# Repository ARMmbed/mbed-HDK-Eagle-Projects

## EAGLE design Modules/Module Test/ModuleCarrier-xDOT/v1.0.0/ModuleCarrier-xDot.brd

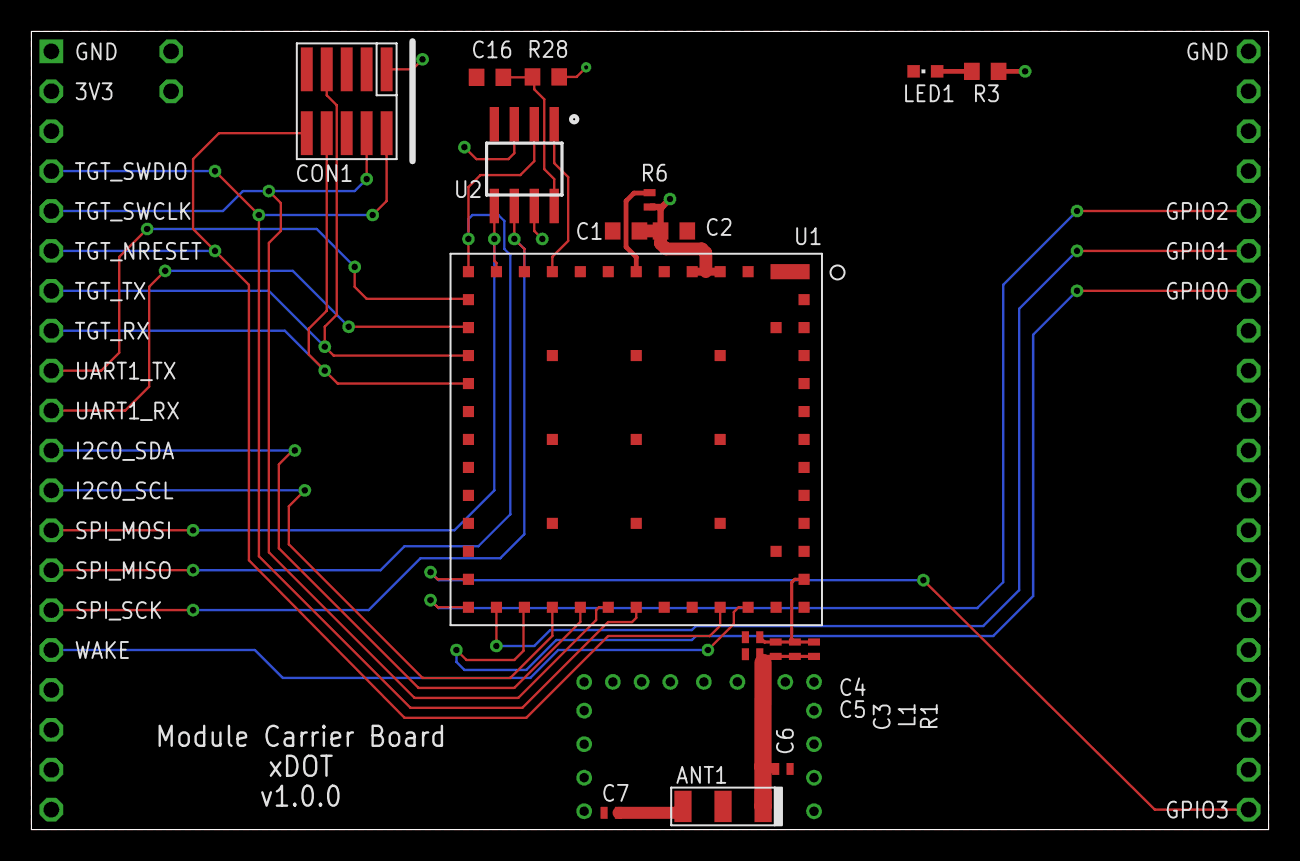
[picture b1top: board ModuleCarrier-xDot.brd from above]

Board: 2 copper layers, 78.7 x 50.8 mm, 21 parts (0 on the bottom side), 26 nets.

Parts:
ANT1: M620720
C1: 10uF; 0603
C2, C16: 100nF; 0603
C3: 9.1pF; 0402
C4: 5.6pF; 0402
C5: 10pF; 0402
C6: 82pF; 0402
C7: 6.8pF; 0402
CON1: SWD-10/TC2050_SMD; FTSH-105-02
L1: 7.5nH; 0402
LED1: SMD_LED0603; CHIPLED_0603
R1, R6: 0; 0402
R3: 1.5K; 0603
R28: 0; 0603
TP1, TP2: TEST-POINT-50R-PTH; TP50-PTH
U1: MTXDOT-EU1-A00-1; MTXDOT-EU1/NA1-A00-1
U2: MX25R3235FM1IH0; SO8
U$1: MODULE_DAUGHTER

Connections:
+3.3V_TGT: C1.1, C2.1, CON1.1, R3.2, R6.1, R28.2, TP1.TP, U1.P$3, U1.P$4, U2.3, U2.7, U$1.2
ANT1: C3.1, C4.2, L1.1, R1.1, U1.P$37
GND: C1.2, C2.2, C4.1, C5.1, C6.1, C7.1, C16.1, CON1.3, CON1.5, CON1.9, LED1.C, TP2.TP, U1.P$1, U1.P$5, U1.P$17, U1.P$20, U1.P$35, U1.P$36, U1.P$38, U1.P$39, U1.P$40, U1.P$41, U1.P$42, U1.P$43, U1.P$44, U1.P$45, U1.P$46, U1.P$48, U1.P$49, U1.P$50, U1.P$51, U1.P$52, U1.P$53, U1.P$54, U1.P$55, U1.P$56, U1.P$57, U1.P$58, U2.4, U$1.1
GPIO0: U1.P$26, U$1.34
GPIO1: U1.P$25, U$1.35
GPIO2: U1.P$24, U$1.36
GPIO3: U1.P$23, U$1.21
I2C0_SCL: U1.P$27, U$1.12
I2C0_SDA: U1.P$28, U$1.11
unnamed: ANT1.P$3, C7.2
unnamed: LED1.A, R3.1
unnamed: ANT1.P$1, C3.2, C5.2, C6.2, L1.2, R1.2
unnamed: C16.2, R28.1, U2.8
RFU2: R6.2, U1.P$6
SPI_MISO: U1.P$12, U2.2, U$1.14
SPI_MOSI: U1.P$11, U2.5, U$1.13
SPI_NSS: U1.P$9, U2.1
SPI_SCK: U1.P$10, U2.6, U$1.15
TGT_NRESET: CON1.10, U1.P$33, U$1.6
TGT_RX: CON1.8, U1.P$16, U$1.8
TGT_SWCLK: CON1.4, U1.P$29, U$1.5
TGT_SWDIO: CON1.2, U1.P$30, U$1.4
TGT_TX: CON1.7, U1.P$15, U$1.7
UART1_RX: U1.P$14, U$1.10
UART1_TX: U1.P$13, U$1.9
WAKE: U1.P$34, U$1.16

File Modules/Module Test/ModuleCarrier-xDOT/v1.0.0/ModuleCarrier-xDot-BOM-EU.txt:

Partlist exported from C:/Users/cstyles/Documents/mbed/Projects/blackbriar/ModuleCarrier-xDot/ModuleCarrier-xDot.sch at 16/11/2017 15:48

Do Not Populate:

	R1
	L1
	C5



Qty Value             Device            Package              Parts   Description                                                                                          MF                      MFN              OC-DIGIKEY    OC-MOUSER         OC-NEWARK
2   0                 RESISTOR0402      0402                 	R1, R6  Resistor                                                                                                                                                                               
1   0                 RESISTOR0603      0603                 	R28     Resistor                                                                                                                                                                               
1   1.5K              RESISTOR0402      0402                 	R3      Resistor                                                                                                                                                                               
2   100nF             CAPACITOR0603     0603                 	C2, C16 Capacitor                                                                                                                                                                              
1   10pF              CAPACITOR0402     0402                 	C5      Capacitor                                                                                                                                                                              
1   10uF              CAPACITOR0603     0603                 	C1      Capacitor                                                                                                                                                                              
1   5.6pF             CAPACITOR0402     0402                 	C4      Capacitor                                                                                                                                                                              
1   6.8pF             CAPACITOR0402     0402                 	C7      Capacitor  (4.7pF for 900MHz/US, 6.8pF for 800MHz/EU)                                                                                                                                                                              
1   7.5nH             INDUCTOR0402      0402                 	L1      Inductor                                                                                                                                                                               
1   82pF              CAPACITOR0402     0402                 	C6      Capacitor                                                                                                                                                                              
1   9.1pF             CAPACITOR0402     0402                 	C3      Capacitor                                                                                                                                                                              
1   M620720           M620720           M620720              	ANT1    Chip Antenna Ceramic ISM/M2M/IoT 868/915MHz                                                          Ethertronics            M620720          939-1066-1-ND                                                                                                                                                                       
1   MTXDOT-EU1-A00-1  MTXDOT-EU1-A00-1  MTXDOT-EU1-A00-1 	U1      Multitech xDOT LORA MODULE UFL/TRC 868MHz for Europe                                                 Multi-Tech Systems Inc. MTXDOT-EU1-A00-1 591-1292-ND                              
1   MX25R3235FM1IH0   MX25R3235FM1IH0   SO8                  	U2      Serial Flash 32 Mb 80 Mhz                                                                            Macronix                MX25R3235FM2IH0  1092-1174-ND                             
1   SMD_LED0603       SMD_LED0603       CHIPLED_0603         	LED2    LED SMD, Colour Red                                                                                  Wurth Electronics Inc   150060RS75000    732-4978-1-ND 710-150060RS75000 2322071  
1   SWD-10/TC2050_SMD SWD-10/TC2050_SMD FTSH-105-02          	CON1    1mm pitch 10-Pin Cortex Programming Header with optional TC2050 footprint solderless interchangeable

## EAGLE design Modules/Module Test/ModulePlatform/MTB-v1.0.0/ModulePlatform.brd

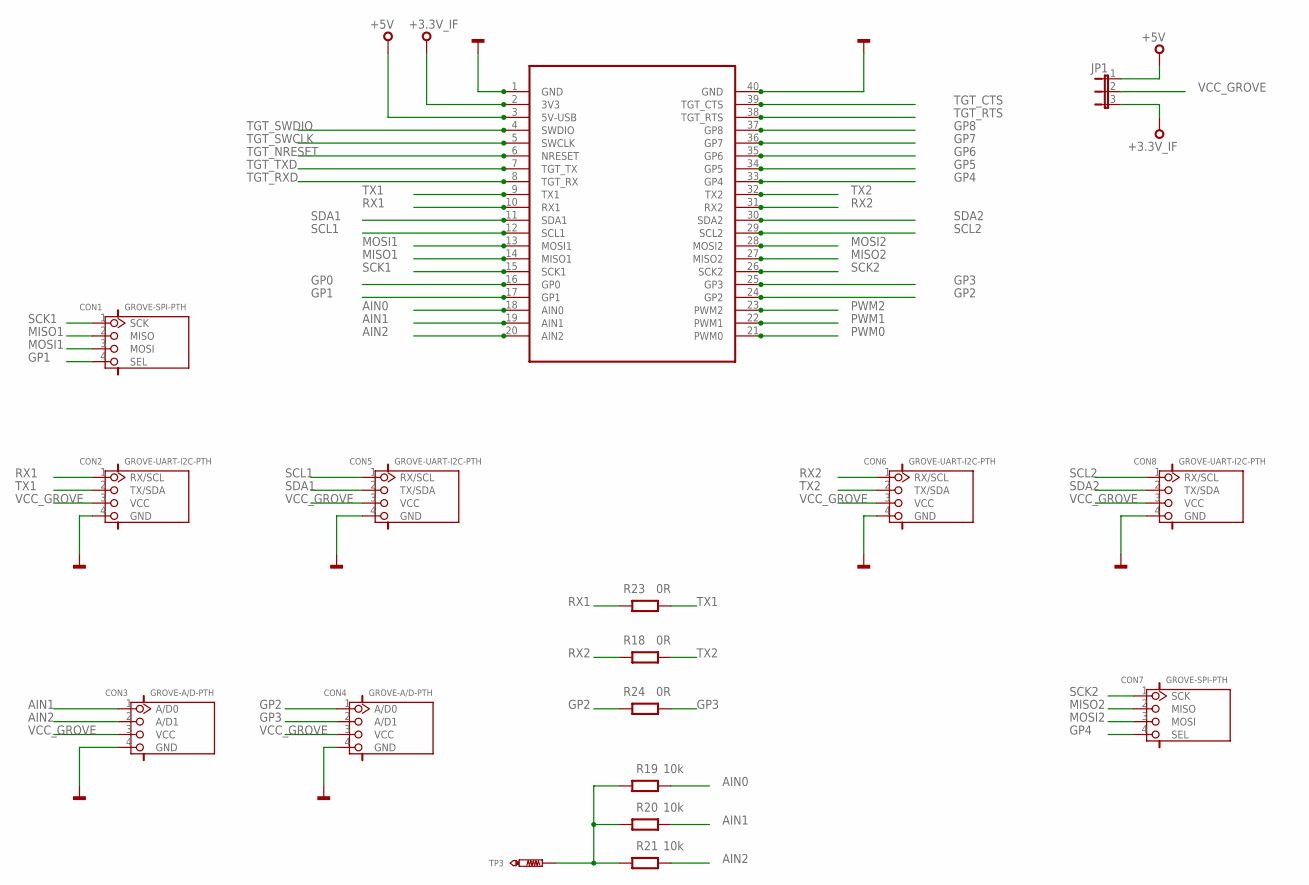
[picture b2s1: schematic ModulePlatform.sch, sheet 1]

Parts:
CON1, CON7: GROVE-SPI-PTH; HW4-2.0
CON2, CON5, CON6, CON8: GROVE-UART-I2C-PTH; HW4-2.0
CON3, CON4: GROVE-A/D-PTH; HW4-2.0
JP1: JP2E; JP2
R18, R23, R24: 0R; 0603@1
R19, R20, R21: 10k; 0603@1
SKT1: MODULE_SOCKET
TP3: TEST-POINT-50R-PTH; TP50-PTH

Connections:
+3.3V_IF: JP1.3, SKT1.2 (3V3), SKT1.P$42; also elsewhere on the board
+5V: JP1.1, SKT1.3 (5V-USB), SKT1.P$43; also elsewhere on the board
AIN0: R19.1, SKT1.18 (AIN0), SKT1.P$58; also elsewhere on the board
AIN1: CON3.1 (A/D0), R20.1, SKT1.19 (AIN1), SKT1.P$59
AIN2: CON3.2 (A/D1), R21.1, SKT1.20 (AIN2), SKT1.P$60
GND: CON2.4 (GND), CON3.4 (GND), CON4.4 (GND), CON5.4 (GND), CON6.4 (GND), CON8.4 (GND), SKT1.1 (GND), SKT1.40 (GND), SKT1.P$41, SKT1.P$80; also elsewhere on the board
GP0: SKT1.16 (GP0), SKT1.P$56; also elsewhere on the board
GP1: CON1.4 (SEL), SKT1.17 (GP1), SKT1.P$57
GP2: CON4.1 (A/D0), R24.2, SKT1.24 (GP2), SKT1.P$64; also elsewhere on the board
GP3: CON4.2 (A/D1), R24.1, SKT1.25 (GP3), SKT1.P$65
GP4: CON7.4 (SEL), SKT1.33 (GP4), SKT1.P$73
GP5: SKT1.34 (GP5), SKT1.P$74; also elsewhere on the board
GP6: SKT1.35 (GP6), SKT1.P$75; also elsewhere on the board
GP7: SKT1.36 (GP7), SKT1.P$76; also elsewhere on the board
GP8: SKT1.37 (GP8), SKT1.P$77
MISO1: CON1.2 (MISO), SKT1.14 (MISO1), SKT1.P$54; also elsewhere on the board
MISO2: CON7.2 (MISO), SKT1.27 (MISO2), SKT1.P$67
MOSI1: CON1.3 (MOSI), SKT1.13 (MOSI1), SKT1.P$53; also elsewhere on the board
MOSI2: CON7.3 (MOSI), SKT1.28 (MOSI2), SKT1.P$68
unnamed: R19.2, R20.2, R21.2, TP3.TP
PWM0: SKT1.21 (PWM0), SKT1.P$61; also elsewhere on the board
PWM1: SKT1.22 (PWM1), SKT1.P$62; also elsewhere on the board
PWM2: SKT1.23 (PWM2), SKT1.P$63; also elsewhere on the board
RX1: CON2.1 (RX/SCL), R23.2, SKT1.10 (RX1), SKT1.P$50
RX2: CON6.1 (RX/SCL), R18.2, SKT1.31 (RX2), SKT1.P$71
SCK1: CON1.1 (SCK), SKT1.15 (SCK1), SKT1.P$55; also elsewhere on the board
SCK2: CON7.1 (SCK), SKT1.26 (SCK2), SKT1.P$66
SCL1: CON5.1 (RX/SCL), SKT1.12 (SCL1), SKT1.P$52; also elsewhere on the board
SCL2: CON8.1 (RX/SCL), SKT1.29 (SCL2), SKT1.P$69; also elsewhere on the board
SDA1: CON5.2 (TX/SDA), SKT1.11 (SDA1), SKT1.P$51; also elsewhere on the board
SDA2: CON8.2 (TX/SDA), SKT1.30 (SDA2), SKT1.P$70; also elsewhere on the board
TGT_CTS: SKT1.39 (TGT_CTS), SKT1.P$79; also elsewhere on the board
TGT_NRESET: SKT1.6 (NRESET), SKT1.P$46; also elsewhere on the board
TGT_RTS: SKT1.38 (TGT_RTS), SKT1.P$78; also elsewhere on the board
TGT_RXD: SKT1.8 (TGT_RX), SKT1.P$48; also elsewhere on the board
TGT_SWCLK: SKT1.5 (SWCLK), SKT1.P$45; also elsewhere on the board
TGT_SWDIO: SKT1.4 (SWDIO), SKT1.P$44; also elsewhere on the board
TGT_TXD: SKT1.7 (TGT_TX), SKT1.P$47; also elsewhere on the board
TX1: CON2.2 (TX/SDA), R23.1, SKT1.9 (TX1), SKT1.P$49
TX2: CON6.2 (TX/SDA), R18.1, SKT1.32 (TX2), SKT1.P$72
VCC_GROVE: CON2.3 (VCC), CON3.3 (VCC), CON4.3 (VCC), CON5.3 (VCC), CON6.3 (VCC), CON8.3 (VCC), JP1.2

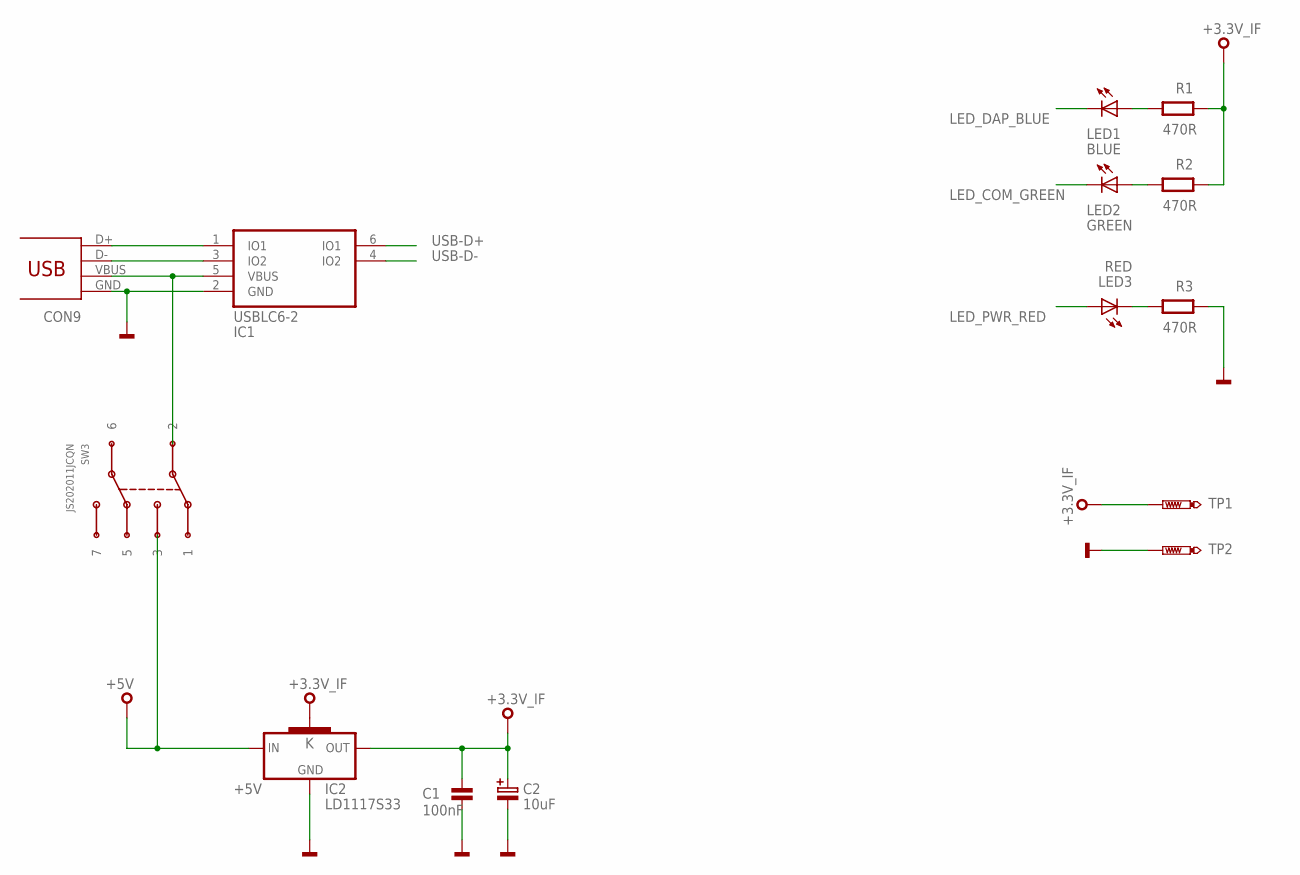
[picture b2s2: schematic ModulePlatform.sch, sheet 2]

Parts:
C1: 100nF; 0603
C2: 10uF; SMC_B
CON9: USB_MICROB; MOLEX-47364-0001
IC1: USBLC6-2SC6; SOT23-6L
IC2: LD1117S33; SOT223
LED1: BLUE; CHIPLED_0603
LED2: GREEN; CHIPLED_0603
LED3: RED; CHIPLED_0603
R1, R2, R3: 470R; 0603@1
SW3: JS202011JCQN
TP1, TP2: TEST-POINT-50R-PTH; TP50-PTH

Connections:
+3.3V_IF: C1.1, C2.+, IC2.2 (OUT), IC2.4 (K), R1.1, R2.1, TP1.TP; also elsewhere on the board
+5V: IC2.3 (IN), SW3.3; also elsewhere on the board
GND: C1.2, C2.-, CON9.GND, IC1.2 (GND), IC2.1 (GND), R3.1, TP2.TP; also elsewhere on the board
LED_COM_GREEN: LED2.C; also elsewhere on the board
LED_DAP_BLUE: LED1.C; also elsewhere on the board
LED_PWR_RED: LED3.A; also elsewhere on the board
unnamed: CON9.D+, IC1.1 (IO1)
unnamed: CON9.D-, IC1.3 (IO2)
unnamed: LED2.A, R2.2
unnamed: LED3.C, R3.2
unnamed: LED1.A, R1.2
unnamed: CON9.VBUS, IC1.5 (VBUS), SW3.2
USB-D+: IC1.6 (IO1); also elsewhere on the board
USB-D-: IC1.4 (IO2); also elsewhere on the board

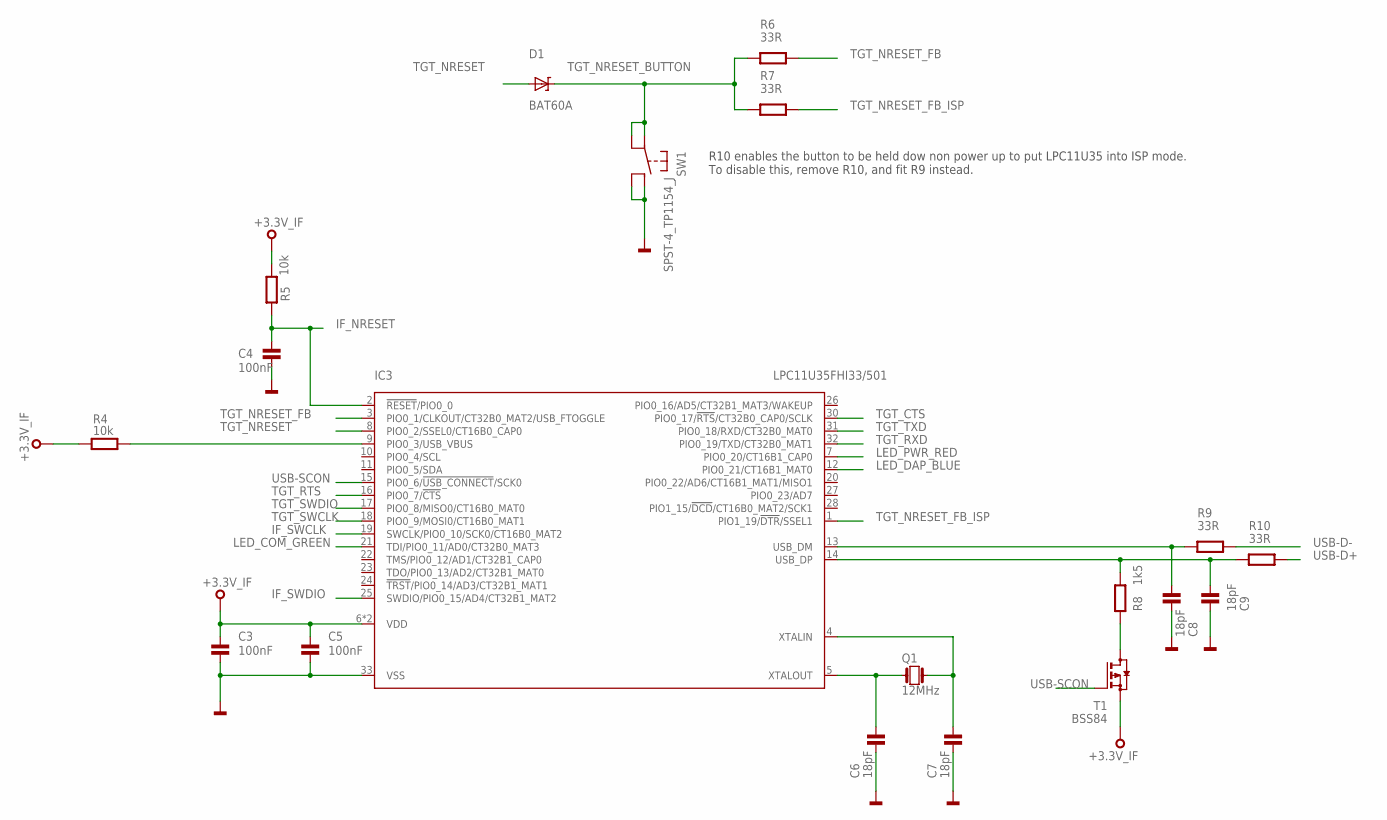
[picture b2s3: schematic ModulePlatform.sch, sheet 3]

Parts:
C3, C4, C5: 100nF; 0603
C6, C7, C8, C9: 18pF; 0603
D1: BAT60A
IC3: LPC11U35FHI33/501; SOT617-3
Q1: 12MHz; 3.2X.2.5
R4, R5: 10k; 0603@1
R6, R7, R9, R10: 33R; 0603@1
R8: 1k5; 0603@1
SW1: SPST-4_TP1154_J; TP-1154X
T1: BSS84; SOT23

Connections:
+3.3V_IF: C3.1, C5.1, IC3.6 (VDD), IC3.29 (VDD), R4.2, R5.2, T1.2 (S); also elsewhere on the board
GND: C3.2, C4.2, C5.2, C6.2, C7.2, C8.2, C9.2, IC3.33 (VSS), SW1.B1, SW1.B2; also elsewhere on the board
IF_NRESET: C4.1, IC3.2 (!RESET!/PIO0_0), R5.1
IF_SWCLK: IC3.19 (SWCLK/PIO0_10/SCK0/CT16B0_MAT2)
IF_SWDIO: IC3.25 (SWDIO/PIO0_15/AD4/CT32B1_MAT2)
LED_COM_GREEN: IC3.21 (TDI/PIO0_11/AD0/CT32B0_MAT3); also elsewhere on the board
LED_DAP_BLUE: IC3.12 (PIO0_21/CT16B1_MAT0); also elsewhere on the board
LED_PWR_RED: IC3.7 (PIO0_20/CT16B1_CAP0); also elsewhere on the board
unnamed: IC3.9 (PIO0_3/USB_VBUS), R4.1
unnamed: C6.1, IC3.5 (XTALOUT), Q1.P$1 (1)
unnamed: C7.1, IC3.4 (XTALIN), Q1.P$3 (2)
unnamed: R8.1, T1.3 (D)
TGT_CTS: IC3.30 (PIO0_17/!RTS!/CT32B0_CAP0/SCLK); also elsewhere on the board
TGT_NRESET: D1.A, IC3.8 (PIO0_2/SSEL0/CT16B0_CAP0); also elsewhere on the board
TGT_NRESET_BUTTON: D1.K, R6.2, R7.2, SW1.A1, SW1.A2
TGT_NRESET_FB: IC3.3 (PIO0_1/CLKOUT/CT32B0_MAT2/USB_FTOGGLE), R6.1
TGT_NRESET_FB_ISP: IC3.1 (PIO1_19/!DTR!/SSEL1), R7.1
TGT_RTS: IC3.16 (PIO0_7/!CTS!); also elsewhere on the board
TGT_RXD: IC3.32 (PIO0_19/TXD/CT32B0_MAT1); also elsewhere on the board
TGT_SWCLK: IC3.18 (PIO0_9/MOSI0/CT16B0_MAT1); also elsewhere on the board
TGT_SWDIO: IC3.17 (PIO0_8/MISO0/CT16B0_MAT0); also elsewhere on the board
TGT_TXD: IC3.31 (PIO0_18/RXD/CT32B0_MAT0); also elsewhere on the board
USB-D+: R10.1; also elsewhere on the board
USB-D-: R9.1; also elsewhere on the board
USB-SCON: IC3.15 (PIO0_6/!USB_CONNECT!/SCK0), T1.1 (G)
USB_DM: C8.1, IC3.13 (USB_DM), R9.2
USB_DP: C9.1, IC3.14 (USB_DP), R8.2, R10.2

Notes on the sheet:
R10 enables the button to be held dow non power up to put LPC11U35 into ISP mode. To disable this, remove R10, and fit R9 instead.

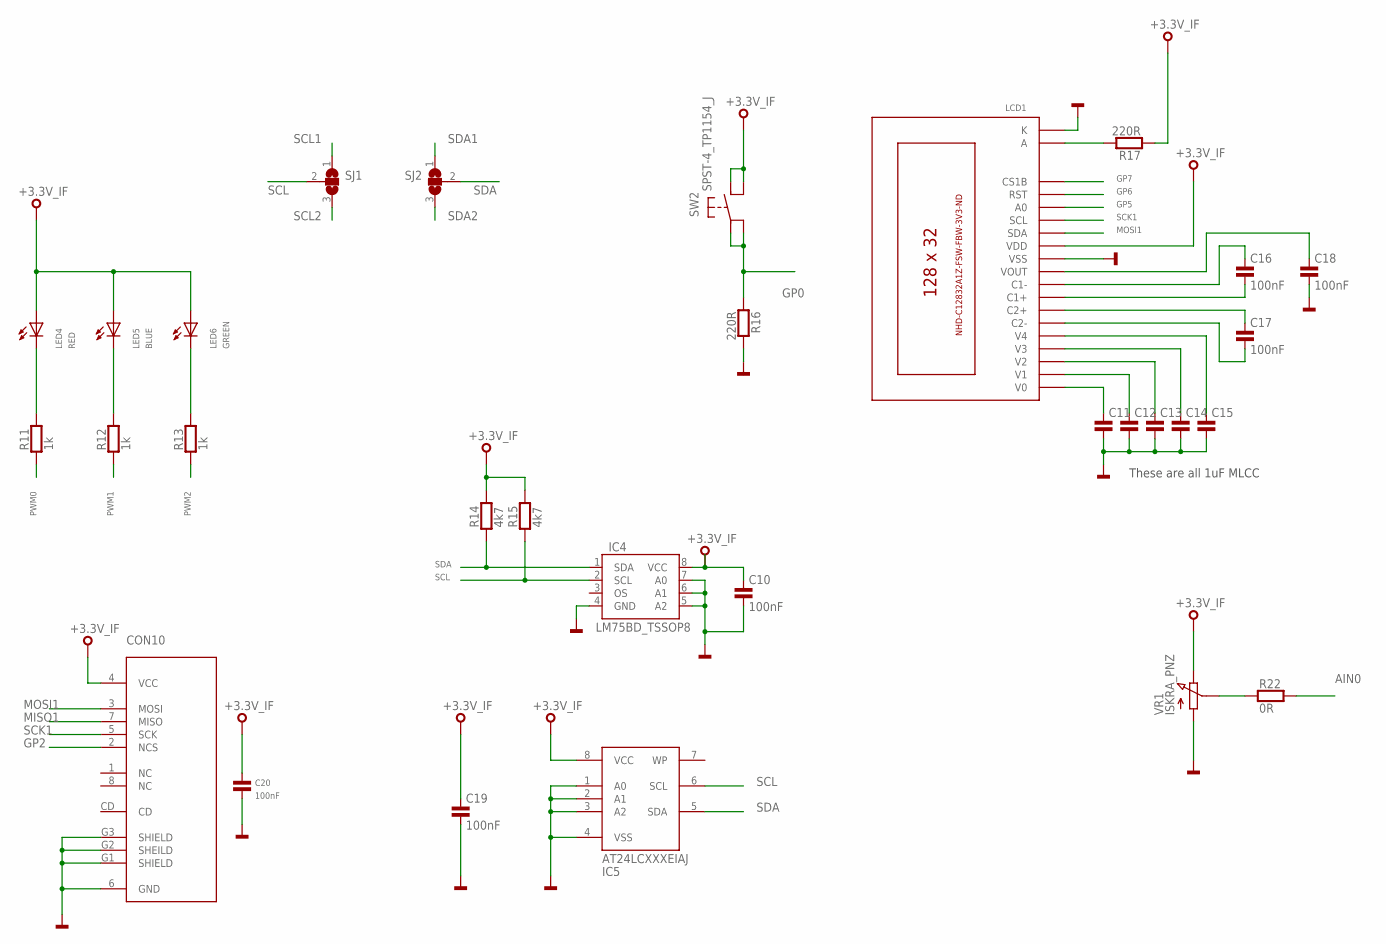
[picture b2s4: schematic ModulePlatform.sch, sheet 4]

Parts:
C10, C11, C12, C13, C14, C15, C16, C17, C18, C19, C20: 100nF; 0603
CON10: MICRO-SD; AMPHENOL-101-00660-68-6
IC4: LM75BD_TSSOP8; TSSOP8
IC5: AT24LCXXXEIAJ; SO08-EIAJ
LCD1: C12832A1Z
LED4: RED; CHIPLED_0603
LED5: BLUE; CHIPLED_0603
LED6: GREEN; CHIPLED_0603
R11, R12, R13: 1k; 0603
R14, R15: 4k7; 0603
R16, R17: 220R; 0603
R22: 0R; 0603
SJ1, SJ2: SJ2W; SJ_2
SW2: SPST-4_TP1154_J; TP-1154X
VR1: ISKRA_PNZ; CA14V

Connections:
+3.3V_IF: C10.1, C19.1, C20.1, CON10.4 (VCC), IC4.8 (VCC), IC5.8 (VCC), LCD1.P$12 (VDD), LED4.A, LED5.A, LED6.A, R14.2, R15.2, R17.1, SW2.B1, SW2.B2, VR1.P$3 (E); also elsewhere on the board
AIN0: R22.2; also elsewhere on the board
GND: C10.2, C11.2, C12.2, C13.2, C14.2, C15.2, C18.2, C19.2, C20.2, CON10.6 (GND), CON10.G1 (SHIELD), CON10.G2 (SHEILD), CON10.G3 (SHIELD), IC4.4 (GND), IC4.5 (A2), IC4.6 (A1), IC4.7 (A0), IC5.1 (A0), IC5.2 (A1), IC5.3 (A2), IC5.4 (VSS), LCD1.K, LCD1.P$11 (VSS), R16.2, VR1.P$1 (A); also elsewhere on the board
GP0: R16.1, SW2.A1, SW2.A2; also elsewhere on the board
GP2: CON10.2 (NCS); also elsewhere on the board
GP5: LCD1.P$15 (A0); also elsewhere on the board
GP6: LCD1.P$16 (RST); also elsewhere on the board
GP7: LCD1.P$17 (CS1B); also elsewhere on the board
MISO1: CON10.7 (MISO); also elsewhere on the board
MOSI1: CON10.3 (MOSI), LCD1.P$13 (SDA); also elsewhere on the board
unnamed: C16.1, LCD1.P$9 (C1-)
unnamed: C17.1, LCD1.P$7 (C2+)
unnamed: C17.2, LCD1.P$6 (C2-)
unnamed: C16.2, LCD1.P$8 (C1+)
unnamed: C11.1, LCD1.P$1 (V0)
unnamed: C12.1, LCD1.P$2 (V1)
unnamed: C13.1, LCD1.P$3 (V2)
unnamed: C14.1, LCD1.P$4 (V3)
unnamed: C15.1, LCD1.P$5 (V4)
unnamed: C18.1, LCD1.P$10 (VOUT)
unnamed: LED4.C, R11.2
unnamed: LED6.C, R13.2
unnamed: LED5.C, R12.2
unnamed: LCD1.A, R17.2
unnamed: R22.1, VR1.P$2 (S)
PWM0: R11.1; also elsewhere on the board
PWM1: R12.1; also elsewhere on the board
PWM2: R13.1; also elsewhere on the board
SCK1: CON10.5 (SCK), LCD1.P$14 (SCL); also elsewhere on the board
SCL: IC4.2 (SCL), IC5.6 (SCL), R15.1, SJ1.2
SCL1: SJ1.1; also elsewhere on the board
SCL2: SJ1.3; also elsewhere on the board
SDA: IC4.1 (SDA), IC5.5 (SDA), R14.1, SJ2.2
SDA1: SJ2.1; also elsewhere on the board
SDA2: SJ2.3; also elsewhere on the board

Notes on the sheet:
These are all 1uF MLCC

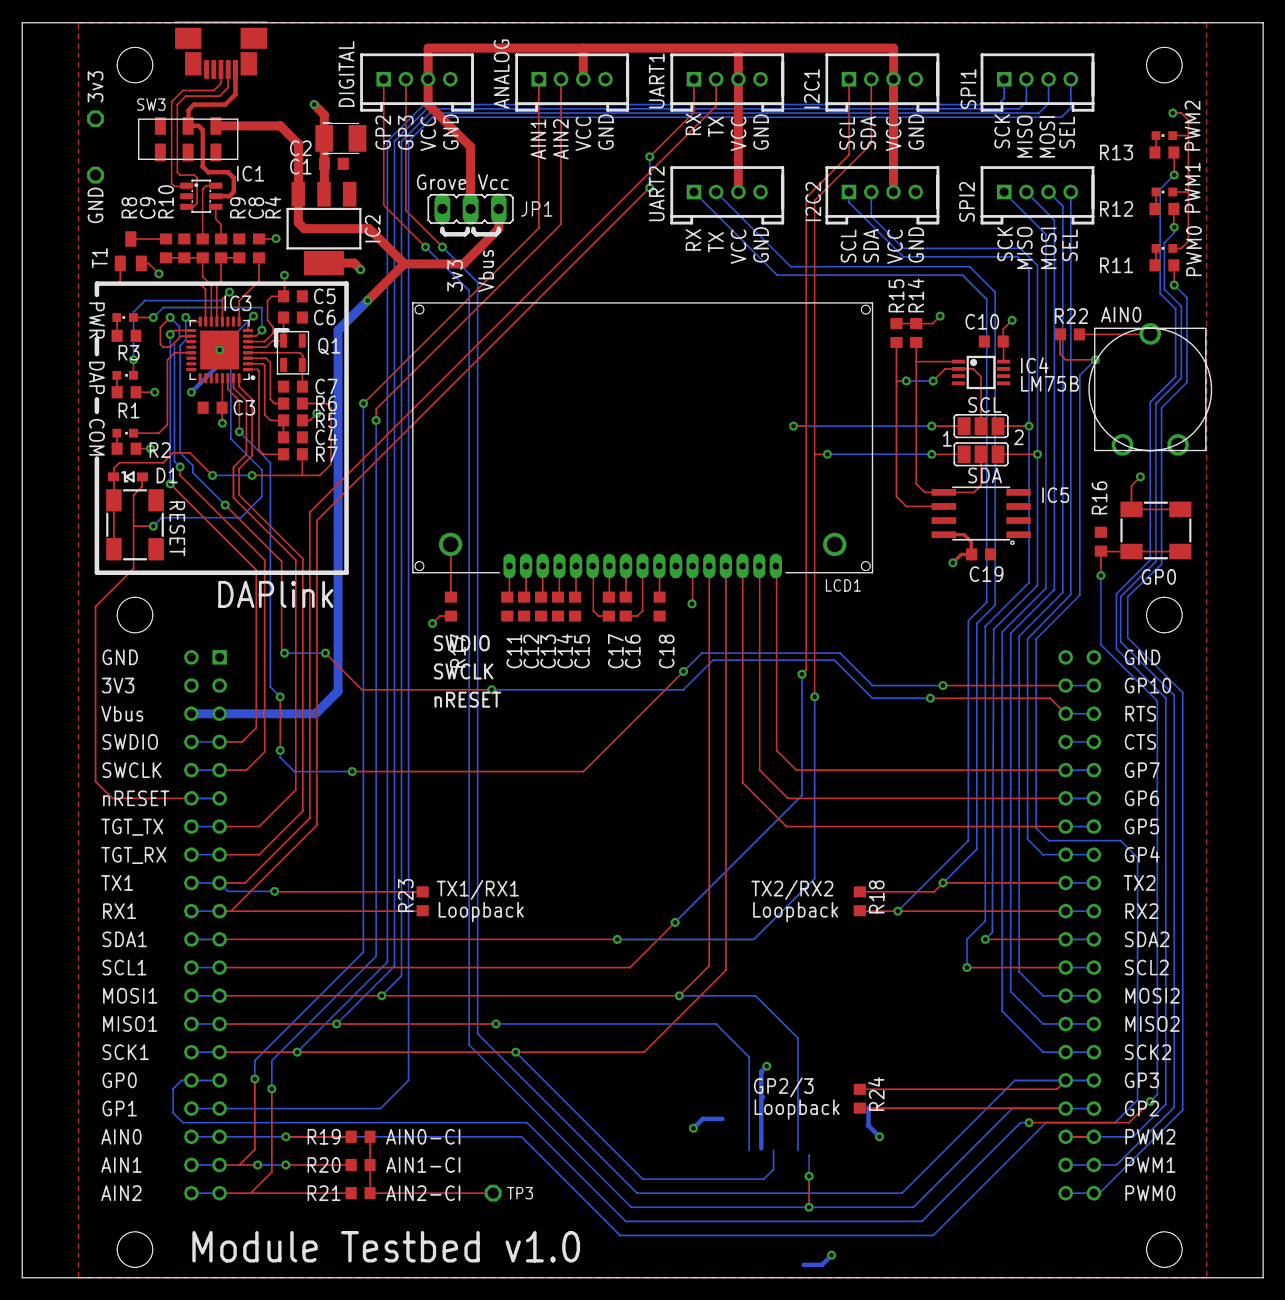
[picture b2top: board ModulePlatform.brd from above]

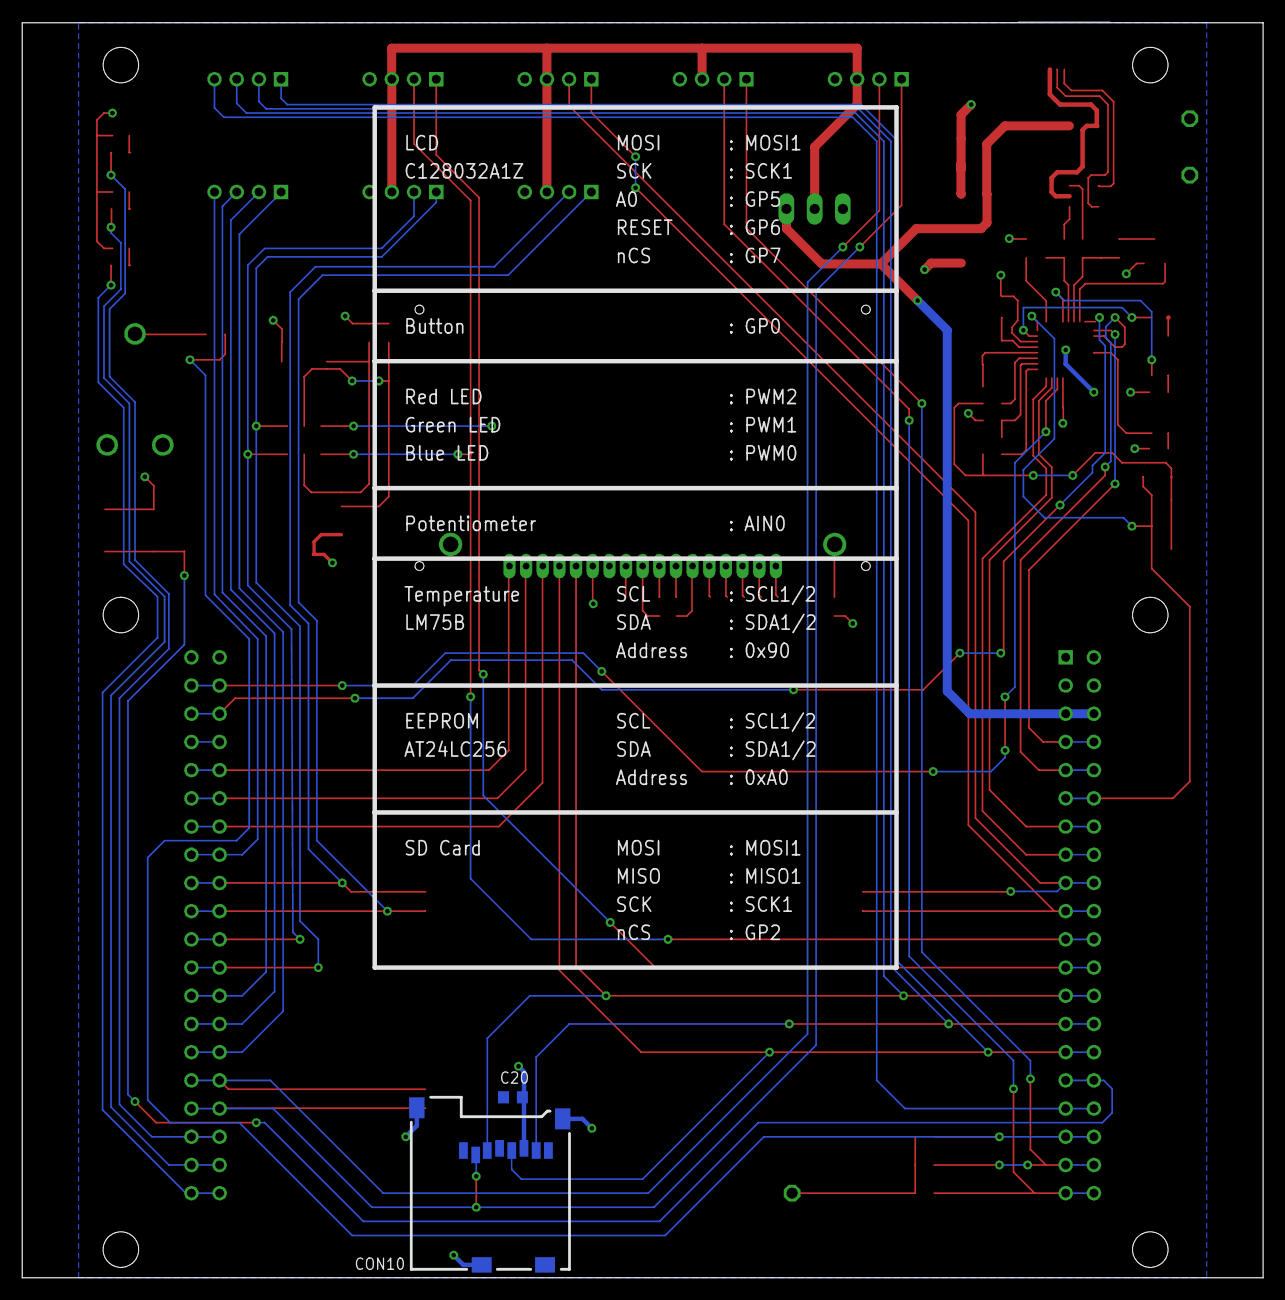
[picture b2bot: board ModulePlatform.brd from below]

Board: 2 copper layers, 111.8 x 113.0 mm, 80 parts (2 on the bottom side), 80 nets.

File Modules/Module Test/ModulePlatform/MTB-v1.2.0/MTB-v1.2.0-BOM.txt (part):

Partlist exported from C:/Users/cstyles/OneDrive - Arm/Documents/mbed/Projects/blackbriar/ModulePlatform/v1.2.0/MTB-v1.2.0.sch at 17/01/2018 10:21

Qty Value              Device             Package                 Parts                                                                 Description                                                                                          
1                      JP2E               JP2                     JP1                                                                   JUMPER                                                                                               
2                      PINHD-1X2          1X02                    JP2, JP3                                                              PIN HEADER                                                                                           
1                      PINHD-2X3          2X03                    JP4                                                                   PIN HEADER                                                                                           
5   0R                 R0603              0603                    R22, R18, R23, R24, R28                                                                                                                                                    
1   0R-DNF             R0603              0603@1                  R30                                                                                                                                                                        
15  100nF              C0603              0603                    C1, C3, C4, C5, C10, C11, C12, C13, C14, C15, C16, C17, C18, C19, C20 Capacitor                                                                                            
8   10k                R0603              0603@1                  R4, R5, R16, R19, R20, R21, R27, R29                                                                                                                                            
1   10uF               C-POLB             SMC_B                   C2                                                                    Polarised capacitor                                                                                  
1   12MHz              Q_3.2X2.5          3.2X.2.5                Q1                                                                                                                                                                         
4   18pF               C0603              0603                    C6, C7, C8, C9                                                        Capacitor                                                                                            
1   1R @ 1%            R0603              0603@1                  R25                                                                                                                                                                        
4   1k                 R0603              0603                    R11, R12, R13, R26                                                                                                                                                         
1   1k5                R0603              0603@1                  R8                                                                                                                                                                                                                                                                                                                                
4   33R                R0603              0603@1                  R6, R7, R9, R10                                                                                                                                                            
4   470R               R0603              0603@1                  R1, R2, R3, R17                                                                                                                                                                 
2   4k7                R0603              0603                    R14, R15                                                                                                                                                                   
1   AT24LCXXXEIAJ      AT24LCXXXEIAJ      SO08-EIAJ               IC5                                                                   I2C EEPROM, 24LC family                                                                              
1   BAT60J             BAT60J            BAT60J                  D1,D2,D3                                                                    Schottky Diode                                                                                       
1   BC850              BC850              SOT23                   T2                                                                    NPN TRANSISTOR                                                                                       
2   BLUE               LED0603            CHIPLED_0603            LED1, LED5                                                            SMD LED                                                                                              
1   BSS84              BSS84              SOT23                   T1                                                                    P-CHANNEL MOS FET                                                                                    
1   C12832A1Z          C12832A1Z          C12832A1Z               LCD1                                                                                                                                                                       
1   FC68148S           FC68148S           FC68148S                CON12                                                                 Power Jack                                                                                           
2   GREEN              LED0603            CHIPLED_0603            LED2, LED6                                                            SMD LED                                                                                              
8   GROVE-A/D-PTH      GROVE-A/D-PTH      HW4-2.0                 CON1,CON2,CON3, CON4, CON5, CON6, CON7, CON8                                                                                                                                                                 
1   ISKRA_PNZ          ISKRA_PNZ          CA14V                   VR1                                                                                                                                                                        
1   JS202011JCQN       JS202011JCQN       JS202011JCQN            SW3                                                                   SLIDE TOGGLE SWITCH VERTICAL (DPDT)                                                                  
1   LD1117S33          LD1117S33          SOT223                  IC2                                                                   VOLTAGE REGULATOR SMD 3,3V                                                                           
1   LM75BD_TSSOP8      LM75BD_TSSOP8      TSSOP8                  IC4                                                                                                                                                                        
1   LPC11U35FHI33/501  LPC11U35FHI33/501  SOT617-3                IC3                                                                   32-bit ARM Cortex-M0 microcontroller; up to 128  kB flash; up                                        
1   MICRO-SD           MICRO-SD           AMPHENOL-101-00660-68-6 CON10                                                                                                                                                                      
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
